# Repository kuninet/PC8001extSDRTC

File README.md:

# PC8001extSDRTC

PC-8001 の外部CPUバスに直結する **PICマイコン式 SDカード + RTC ドライブ** の設計資料リポジトリです。

SDアクセスを、PC-8001 のCPU外部バスに接続した **PIC18F47Q43** に肩代わりさせ、SDカードを
**Z80 の I/O デバイス**として見せます。将来は I2C RTC(DS3231等)も同じデバイスに同居させます。

ソフト側(SD-DOS)から見ると、SDアクセス下回りのドライバ(`MMC.asm`)を I/O ポート版
(`MMC_PIC.asm`)に差し替えるだけで使えます。上位のファイルシステム層は無変更です。

- ソフト本体(SD-DOS): https://github.com/kuninet/SD-DOS
- I/O プロトコル仕様(最重要): [docs/protocol.md](docs/protocol.md)
- 兄弟プロジェクト(同じ外部バス直結の流儀): [PC8001ext232C](https://github.com/kuninet/PC8001ext232C)

> ⚠️ 本リポジトリは **設計段階**です。回路・基板・PICファームはこれから物理試作します。
> まずは I/O プロトコルと、SD-DOS 側のドライバ差し替え構成を固める段階です。

## なぜ作るのか(背景)

SD-DOS の SDアクセスは 8255 PPI を使った **ビットバンギング SPI** です。これは1セクタ
(512バイト)の読み出しに実機(Z80 実効約1.84MHz)で **約0.1秒**かかり、密に音符が並ぶ
VGM再生などでは「もたつき」が出ます(Issue #68 の割り込み駆動プレイヤ検証で、ソフトの
工夫では消せないと結論)。

そこで下回りを **ハードSPI(MHz級)を持つPIC**に置き換えると、1セクタ読みが **~0.5ms** 前後、
**約200倍**高速化します。同期読みのままでももたつかなくなり、割り込み背景読みのような
小細工も不要になります。

## 設計方針(A案: 生512Bブロックデバイス)

PIC は **「512バイト単位のランダムアクセス I/O デバイス」**に徹します。

- FAT 等のファイルシステムは **Z80(SD-DOS)側**のまま。PIC は生ブロックの R/W だけを担う。
- CP/M など他のソフトからも汎用的に使える(ファイルシステム非依存)。
- PIC は周辺を全エミュレートするのではなく、**I/O 周辺デバイスに徹する**。
  クロック・主ROM・主RAM は PC-8001 が供給する(EMUZ80 とは役割が逆)。

## アーキテクチャ

```mermaid
flowchart LR
    subgraph PC["PC-8001 外部CPUバス (5V)"]
        BUS["A0-A7 / D0-D7<br/>/IORQ /RD /WR /RESET"]
        WAIT["/WAIT (PICが駆動)"]
    end

    PIC["PIC18F47Q43<br/>I/Oポートデコード (D0H-D6H)<br/>512B セクタバッファ<br/>コマンド/データ/ステータス"]
    SD["microSD"]
    RTC["RTC DS3231 (将来)"]

    BUS <-->|"A0-A7 / D0-D7 / 制御"| PIC
    PIC -->|"/WAIT ハンドシェイク"| WAIT
    PIC <-->|SPI| SD
    PIC <-.->|I2C| RTC
```

I/O ポートは PC-8001 未割り当ての拡張領域 **D0H-D6H** に割り当てます。
詳細は [docs/protocol.md](docs/protocol.md) を参照してください(SD-DOS と共有する契約)。

| ポート | R/W | 役割 |
|---|---|---|
| D0H | W | コマンド(0=READ, 1=WRITE, 2=STATUS, 3=INIT、将来RTC) |
| D1H-D4H | W | セクタアドレス 32bit(LSB→MSB) |
| D5H | R/W | データFIFO(512B セクタバッファ ストリーム入出力) |
| D6H | R | ステータス(bit0=READY, bit1=BUSY, bit7=ERROR) |

### タイミングの見積り

実効1.84MHz → 1 I/O サイクル ≒ 2.2μs。PIC を64MHzで回すと **約35命令ぶん**の猶予があり、
EMUZ80 の 1350ns/21命令より約5倍楽です。単純なレジスタ応答は /WAIT 無しでも届く見込みですが、
**/WAIT で安全マージンを取る**設計にします。遅いSD読み中(~0.5ms)はZ80を /WAIT で固めず、
ステータスを polling して待つ方式とし、N-BASIC の割り込みを止めません。

## PIC を PIC18F47Q43 にする理由

| 型番 | RAM | Flash | MaxMHz | CLC | 備考 |
|---|---|---|---|---|---|
| **PIC18F47Q43(採用)** | 8KB | 128KB | 64 | あり | 512Bバッファ後も余裕、EMUZ80 実績、SPI×2/I2C |
| PIC18F46K22 | 4KB | 64KB | 64 | なし | バッファは足りるが余裕減、デコード外付け要かも |
| PIC18F4550 以下 | ≤2KB | ≤32KB | ≤48 | なし | 512Bバッファでほぼ埋まる(非推奨) |

RAM 8KB は 512B セクタバッファ + 将来のダブルバッファ / FATキャッシュ余地に効きます。
CLC(Configurable Logic Cell)で I/O ポートデコードをハード化でき、応答に余裕が出ます。

## SD-DOS 側のビルド分け

SD-DOS は **ビットバンギング(既定)** と **PICSD** を同一ソースから作り分けます。

- `src/LABELS.asm` の `USE_PICSD EQU FALSE`(既定)を `TRUE` にすると PIC版になる。
- `src/MMC.asm`(8255ビットバンギング)/ `src/MMC_PIC.asm`(D0H-D6H I/O)を条件INCLUDEで切替。
- ビルド: 既定 `make` がビットバンギング、`make picsd` が PIC版(`build/MAIN-PICSD.cmt`)。

詳細は SD-DOS リポジトリを参照してください。

## ロードマップ

1. **/WAIT 実機検証(最優先)**: 最小PICで「D0H 読み書きエコー + /WAIT アサート/解除」だけ作り、
   PC-8001 外部バスが /WAIT を尊重するか実機確認する。
2. **PIC SDファーム**: SPI初期化 + CMD17/CMD24 でセクタ R/W、512Bバッファ、ステータス。
   ロジックアナライザで I/O プロトコルを確認する。
3. **SD-DOS `MMC_PIC.asm` 結合**: Mac側の回帰テストをフック差し替えで通し、実機で R/W。
4. **実機体感**: VGMPLAY で「もたつき消滅」を確認(本丸)。
5. **RTC フェーズ**: D0H コマンドに時計 R/W を追加、I2C DS3231 等。

## ディレクトリ構成

```
PC8001extSDRTC/
├── README.md          このファイル(設計概要)
├── Makefile           PC-8001側テスト(WAITTEST)ビルド / firmware構文チェック
├── tools/             外部ツール(tools80.jar を置く。本体は再配布しないため非コミット)
├── docs/
│   └── protocol.md    D0H-D6H I/O 仕様(SD-DOS と共有する契約。最重要)
├── hardware/
│   └── design.md      回路設計仕様・結線表・ピンアサイン・BOM
├── firmware/          PIC18F47Q43 ファーム(MPLAB X / XC8)。今は構成と関数スタブ
│   └── waittest/      /WAIT 検証用スタブ
└── test/              /WAIT ハンドシェイク検証(PC-8001側 WAITTEST.asm + 手順)
```

## ビルド

PC-8001 アセンブラ tools80.jar を `tools/` に置きます(入手方法は [tools/README.md](tools/README.md)。
ツール本体は再配布しないためリポジトリには含めません)。SD-DOS など他リポジトリには依存しません。

```sh
make            # build/WAITTEST.cmt(PC-8001側 /WAIT 検証)を生成
make fw-check   # firmware の C スタブをホストで構文チェック
```

別の場所の jar を使う場合は `make TOOLS80=/path/to/tools80.jar`。PIC ファーム本体の実機
ビルドは MPLAB X + XC8 で行います。

## 将来検討: PC-80S31(FD)互換モード

PIC+SD を PC-80S31(NEC純正フロッピーユニット)のホストインターフェースに似せれば、
無改造の N-BASIC DISK BASIC / NEC CP/M が動く可能性があります(膨大な .D88 資産が使える)。
ただし PC-80S31 は Z80+μPD765 を積んだ知的サブシステムで、互換ファームは A案の単純な
ブロックデバイスより遥かに重く、フロッピー意味論に制約されます。**当面は A案を主とし、
PIC がバス上にいる利点を活かして将来「モード」として追加し得る**設計に留めます。

## ライセンス

MIT License. [LICENSE](LICENSE) を参照してください。

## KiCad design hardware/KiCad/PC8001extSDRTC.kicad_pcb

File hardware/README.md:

# hardware — 回路図・基板(設計メモ)

PC-8001 外部CPUバスに直結する PIC18F47Q43 ボードのハードウェア設計です。
回路図・基板は KiCAD で起こす予定です(本ディレクトリに追加)。

- **[design.md](design.md) … 回路設計仕様・結線表(フェーズA)。基本方針・ブロック図・
  ピンアサイン表・ネット単位の結線表・BOM。KiCAD はこの結線表をもとに引く。**

## 接続するバス信号(PC-8001 拡張バス → PIC)

- アドレス: `A0`-`A7`(I/O ポートデコード用。`D0H`-`D6H` を識別)
- データ: `D0`-`D7`(双方向。PIC が `IN` 時にドライブ)
- 制御: `/IORQ`, `/RD`, `/WR`, `/RESET`
- `/WAIT`: **PIC が駆動**(オープンコレクタ/オープンドレインで Wired-OR)

## PIC 側ペリフェラル

- microSD: ハードSPI(MSSP1)。CS/SCK/MOSI/MISO。
- (将来)RTC: I2C(MSSP2)。DS3231 等。SDA/SCL に 4.7kΩ プルアップ。
- I/O デコード: CLC(Configurable Logic Cell)で `A7..A0 == D0H..D6H` かつ `/IORQ` を
  ハード判定し、応答レイテンシを詰める。

## 検討事項(要実機検証)

- **/WAIT を PC-8001 拡張バスが尊重するか**(最優先)。尊重しない場合の回避策はソフト側で。
- データバス バッファ(74xx245 等)の向き制御を `/RD`・デコード出力で行うか、PIC直結か。
- 5V(PC-8001)と 3.3V(SD/PIC)のレベル変換。PIC18F47Q43 は 5V 動作可だが、SD は 3.3V。
- 拡張バスのバスタイミング(セットアップ/ホールド)の実測(ロジックアナライザ)。

## ポートマップ

I/O ポート割り当て(`D0H`-`D6H`)は [../docs/protocol.md](../docs/protocol.md) を参照。

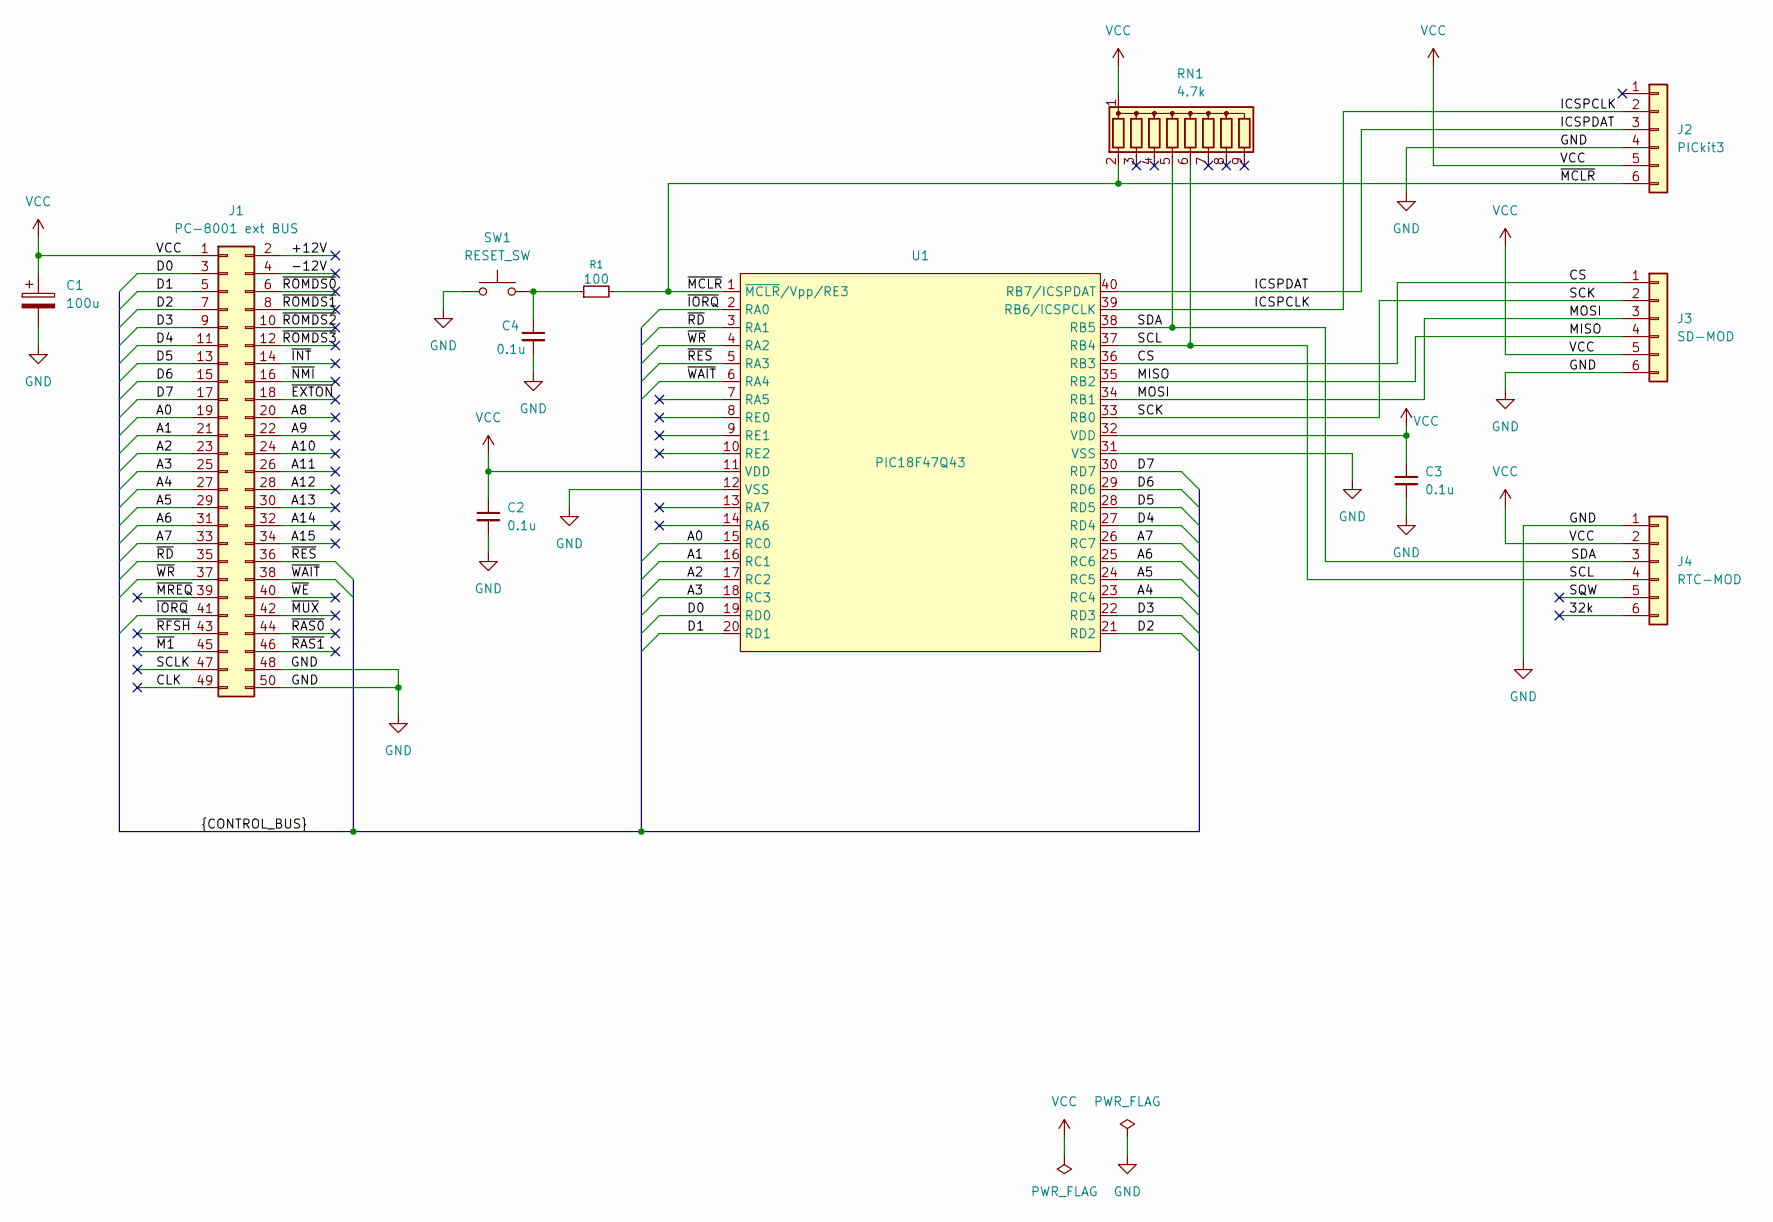
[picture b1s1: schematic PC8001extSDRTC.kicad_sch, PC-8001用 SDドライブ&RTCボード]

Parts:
C1: 100u
C2, C3, C4: 0.1u
J1: PC-8001 ext BUS
J2: PICkit3
J3: SD-MOD
J4: RTC-MOD
R1: 100
RN1: 4.7k; R_Array_SIP9
SW1: RESET_SW
U1: PIC18F47Q43

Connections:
/32k: J4.6
/+12V: J1.2
/-12V: J1.4
/A0: J1.19, U1.15 (RC0)
/A1: J1.21, U1.16 (RC1)
/A2: J1.23, U1.17 (RC2)
/A3: J1.25, U1.18 (RC3)
/A4: J1.27, U1.23 (RC4)
/A5: J1.29, U1.24 (RC5)
/A6: J1.31, U1.25 (RC6)
/A7: J1.33, U1.26 (RC7)
/A8: J1.20
/A9: J1.22
/A10: J1.24
/A11: J1.26
/A12: J1.28
/A13: J1.30
/A14: J1.32
/A15: J1.34
/CLK: J1.49
/CS: J3.1, U1.36 (RB3)
/D0: J1.3, U1.19 (RD0)
/D1: J1.5, U1.20 (RD1)
/D2: J1.7, U1.21 (RD2)
/D3: J1.9, U1.22 (RD3)
/D4: J1.11, U1.27 (RD4)
/D5: J1.13, U1.28 (RD5)
/D6: J1.15, U1.29 (RD6)
/D7: J1.17, U1.30 (RD7)
/ICSPCLK: J2.2, U1.39 (RB6/ICSPCLK)
/ICSPDAT: J2.3, U1.40 (RB7/ICSPDAT)
/MISO: J3.4, U1.35 (RB2)
/MOSI: J3.3, U1.34 (RB1)
/SCK: J3.2, U1.33 (RB0)
/SCL: J4.4, RN1.6 (R5), U1.37 (RB4)
/SCLK: J1.47
/SDA: J4.3, RN1.5 (R4), U1.38 (RB5)
/SQW: J4.5
/~EXTON: J1.18
/~INT: J1.14
/~IORQ: J1.41, U1.2 (RA0)
/~M1: J1.45
/~MCLR: J2.6, R1.2, RN1.2 (R1), U1.1 (~MCLR/Vpp/RE3)
/~MREQ: J1.39
/~MUX: J1.42
/~NMI: J1.16
/~RAS0: J1.44
/~RAS1: J1.46
/~RD: J1.35, U1.3 (RA1)
/~RES: J1.36, U1.5 (RA3)
/~RFSH: J1.43
/~ROMDS0: J1.6
/~ROMDS1: J1.8
/~ROMDS2: J1.10
/~ROMDS3: J1.12
/~WAIT: J1.38, U1.6 (RA4)
/~WE: J1.40
/~WR: J1.37, U1.4 (RA2)
GND: C1.2, C2.2, C3.2, C4.2, J1.48, J1.50, J2.4, J3.6, J4.1, SW1.1, U1.12 (VSS), U1.31 (VSS)
unnamed: C4.1, R1.1, SW1.2
VCC: C1.1, C2.1, C3.1, J1.1, J2.5, J3.5, J4.2, RN1.1 (common), U1.11 (VDD), U1.32 (VDD)

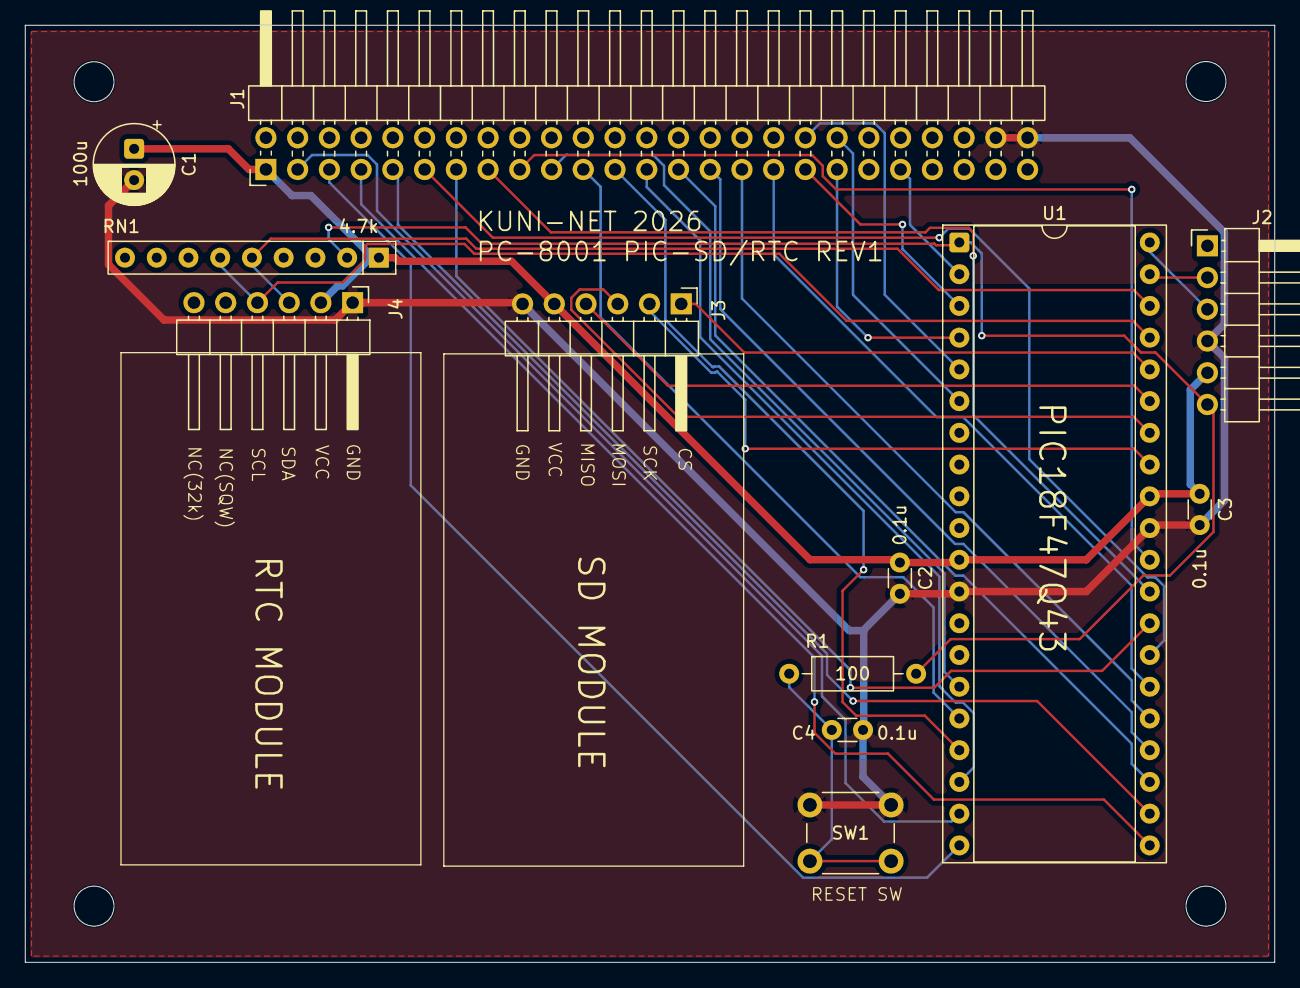
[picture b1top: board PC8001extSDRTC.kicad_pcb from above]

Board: 2 copper layers, 100.0 x 75.0 mm, 16 parts (0 on the bottom side), 33 nets.

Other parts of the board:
H1, H2, H3, H4: MountingHole; MountingHole_3.2mm_M3

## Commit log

2026-06-20 PC8001extSDRTC 初期設計資料を追加
    - README: 設計概要(A案=生512Bブロックデバイス・PIC18F47Q43・タイミング根拠・ロードマップ)
    - docs/protocol.md: D0H-D6H I/O 契約(SD-DOS と共有する真実)
    - hardware/: バス直結・/WAIT・SPI・I2C の方針メモ
    - firmware/: PIC18F47Q43 ファーム構成と picsd_main.c スタブ
    - LICENSE(MIT) / .gitignore
2026-06-20 docs(hardware): 回路設計仕様・結線表(フェーズA)を追加 #5
    PIC18F47Q43 を 5V 単一電源でバス直結する方針で、ブロック図・ピンアサイン表
    (PDIP-40)・ネット単位の結線表・BOM を確定。
    - 基本方針: PIC@5V でバス側レベル変換を不要化。3.3V は microSD モジュールの
    オンボード変換に委譲。RTC(DS3231)は 5V 直結。内部64MHz・水晶不要。
    - ピンアサイン: A0-A7=PORTB / D0-D7=PORTD / 制御=PORTA(/WAIT=RA4 OD) /
    SPI=RC0-2+RC5 / I2C=RC3/RC4(将来)
2026-06-20 docs: ブロック図を Mermaid 化(README / hardware/design.md)
    ASCIIアートをやめ、GitHub で描画される Mermaid flowchart に置き換えて視認性を上げる。
2026-06-20 test: /WAIT 検証用の最小プログラム一対を追加 #1
    PC-8001拡張バスが /WAIT を尊重するかを SD/RTC 抜きで確かめる。
    - test/WAITTEST.asm: PC-8001側。テストポート(既定D0H)を IN/OUT し
    "RD=xx NG=nnn WR=yy" を表示(RST18H)。NG=0かつRD=55,WR=A5で合格。
    tools80でアセンブル確認済み(LOAD→G9000→BASIC復帰)。
    - firmware/waittest/waittest.c: PIC側スタブ。/WAITを下げて意図的に遅延し
    last(=55H)を返す/取り込む。実機ピンはdesign.md準拠で要実装。
2026-06-20 build: ビルド用 Makefile を追加
    - make / make waittest: PC-8001側 WAITTEST.asm を tools80 でアセンブルし build/ へ
    - make fw-check: firmware の C スタブをホストコンパイラで構文チェック
    - TOOLS80 は既定 ../SD-DOS/tools/tools80.jar(同階層前提、上書き可)
    - README / test/README に make 手順を反映
2026-06-20 build: tools80 を tools/ 参照にして SD-DOS 非依存に
    ExtSD 単体でビルドできるよう、Makefile の既定 TOOLS80 を tools/tools80.jar に変更。
    jar 本体は再配布しないため非コミット(.gitignore、入手方法は tools/README.md)。
    SD-DOS と同じ流儀。
    - tools/README.md: tools80.jar の入手方法
    - .gitignore: /tools/*(!README.md)、test/*.cmt を追加
    - Makefile: TOOLS80 ?= tools/tools80.jar
2026-06-20 docs(hardware): ピンアサインをデータシート(DS40002147E)で確定
    PIC18F47Q43 PDIP-40 のピン番号を Figure 2-3 / Table 3-2「40-Pin PDIP」と照合し一致を確認。
    SPI(SCK1/SDO1/SDI1)はPPS再配置可でRC0-RC2、I2CはI2C専用レベルpinのRC3/RC4(Note4)を採用。
    MCLR推奨回路(10kΩ+100〜470Ω直列+0.1µF)とICSP共有(RB6/RB7=A6/A7)をBOM/注記に反映。
    要照合→照合済みに更新。残課題は実機(/WAITタイミング・バスバッファ・ICSP分離)。
2026-06-20 chore: 外部資料用 external/ を追加(git非管理)
    データシート等の第三者配布物を置くフォルダ。本体は再配布しないため非コミット
    (.gitignore、入手方法は external/README.md)。tools/ と同じ流儀。
2026-06-21 design: ピンアサイン見直し(A0-A7=PORTC, SPI/I2C=PORTB, RB6/7=ICSP専用)
    ICSP(RB6/RB7)と拡張アドレスの衝突を構造的に排除するため、A0-A7をPORTCへ移し
    SPI/I2CをPORTBへ移設。RB6/RB7はアプリ未使用のICSP専用とし、挿したままでも
    抜いても書込競合なし。トレードはI2C専用レベルpin(RC3/RC4のみ)をアドレスに
    使う点で、I2Cは標準STレベル動作(将来RTCで実機確認)。SD_CSプルアップ・RB6/7
    フロート対策も注記。
2026-06-21 docs: ICSP弱プルアップは内部WPU/外付け不可を明記、/WAITは母板プルアップ前提に修正
    回路レビューでの誤解(ICSPCLK/DATに外付けプルアップを付けてしまう)を防ぐため、
    RB6/RB7のフロート回避は内部弱プルアップ(WPUB)で行い外付けはNGと明記。
    /WAITはPC-8001母板側でプルアップ済みのためボード側不要(BOM数0・§6更新)。
2026-06-21 feat: KiCad回路図を追加(PIC18F47Q43 / PC-8001拡張バス / SD / RTC / ICSP) #6
    フェーズA(#5)のピンアサイン・結線表どおりに回路図を入力。ネットリスト突合で
    PIC全40ピンがdesign.mdと一致、ERC0件を確認。MCLR/ICSPはR1直列分離でPGC/PGD
    クリーン、/WAITはPC-8001母板プルアップ前提。.gitignoreにKiCadのローカル設定/
    バックアップ/履歴を追加し、本体(pro/sch/pcb)とカスタムシンボルのみ追跡。
2026-06-24 feat: PCBレイアウト完成・製造用ガーバー一式を追加 #7
    回路図(#6)をもとに2層基板(100x75mm)を配線。両面GNDベタ、電源0.6mm/信号0.2mm、
    パスコンを各VDDピン至近(4mm前後)に配置。DRC 0違反・未配線0。
    製造データ(Gerber X2/mm/4.6 + Excellonドリル + zip)を hardware/KiCad/PCB/ に同梱。
    ガーバーは現行.kicad_pcbと幾何一致を確認済み。
    .gitignoreにFreerouting中間(dsn/ses/rules)と空ライブラリを追加。
2026-06-28 feat: /WAIT検証ファーム(waittest)を実装しXC8ビルド対応 #1
    - firmware/waittest/waittest.c: スタブから実装へ。
    - 内部64MHz HFINTOSC・config一式(WDT無効/LVP=ON 等)
    - ポート初期化: /IORQ・/RD・/WR・/RESET=RA0-3、/WAIT=RA4(ODCONでOD)、
    A0-A7=PORTC、D0-D7=PORTD(READ時のみ出力)
    - ポーリング処理: /IORQ→自ポート(D0H)宛のみ /WAIT を下げて整流。
    READ=遅延→last出力→/RD解放まで保持、WRITE=整流→取り込み。
